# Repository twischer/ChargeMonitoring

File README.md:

ChargeMonitoring
================

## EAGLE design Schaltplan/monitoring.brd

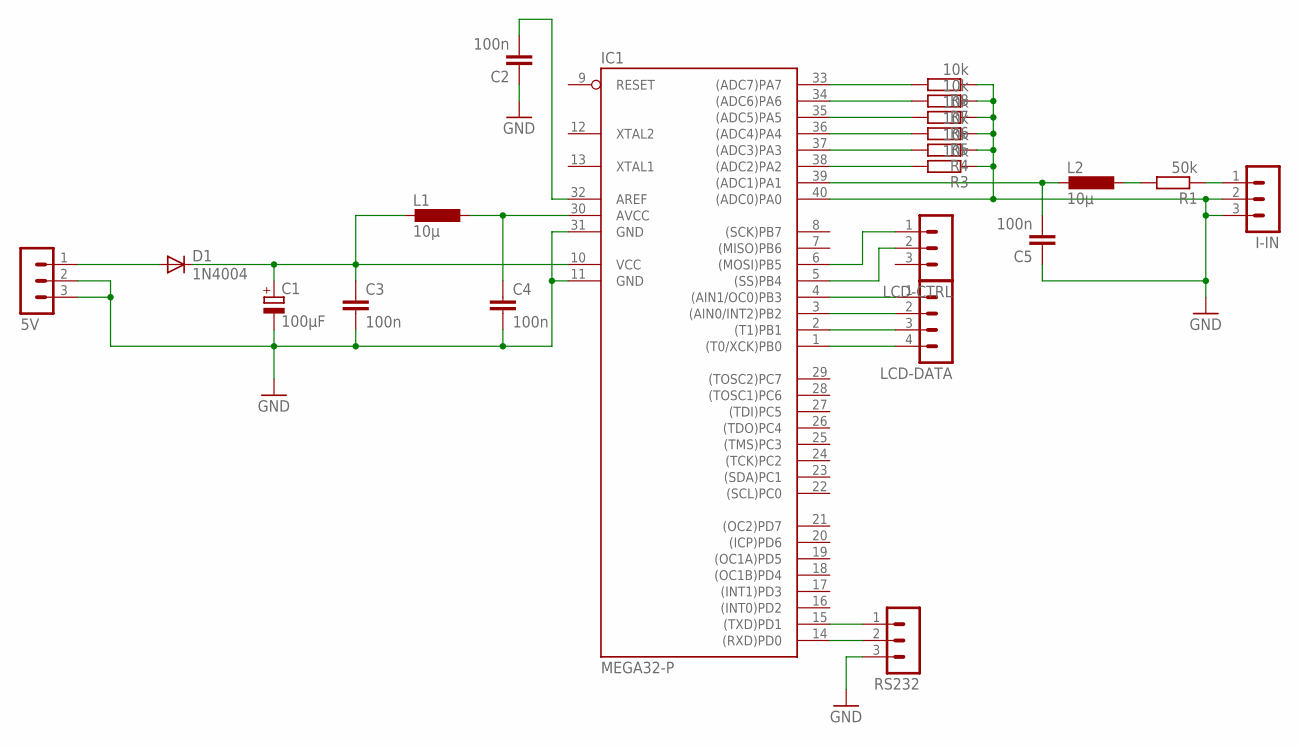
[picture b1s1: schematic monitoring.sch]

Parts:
5V: MA03-1
C1: 100µF; E5-10,5
C2, C3, C4, C5: 100n; C050-035X075
D1: 1N4004; DO41-10
I-IN: MA03-1
IC1: MEGA32-P; DIL40
L1: 10µ; 0204V
L2: 10µ; 0207/10
LCD-CTRL: MA03-1
LCD-DATA: MA04-1
R1: 50k; 0204V
R3, R4, R5, R6, R7, R8: 10k; 0204V
RS232: MA03-1

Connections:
GND: 5V.2, 5V.3, C1.-, C2.1, C3.2, C4.2, C5.1, I-IN.2, I-IN.3, IC1.11 (GND), IC1.31 (GND), IC1.40 ((ADC0)PA0), R3.1, R4.1, R5.1, R6.1, R7.1, R8.1, RS232.3
unnamed: IC1.4 ((AIN1/OC0)PB3), LCD-DATA.1
unnamed: C1.+, C3.1, D1.C, IC1.10 (VCC), L1.2
unnamed: IC1.38 ((ADC2)PA2), R3.2
unnamed: IC1.3 ((AIN0/INT2)PB2), LCD-DATA.2
unnamed: C5.2, IC1.39 ((ADC1)PA1), L2.2
unnamed: IC1.37 ((ADC3)PA3), R4.2
unnamed: IC1.2 ((T1)PB1), LCD-DATA.3
unnamed: IC1.1 ((T0/XCK)PB0), LCD-DATA.4
unnamed: IC1.5 ((SS)PB4), LCD-CTRL.2
unnamed: IC1.6 ((MOSI)PB5), LCD-CTRL.1
unnamed: 5V.1, D1.A
unnamed: IC1.36 ((ADC4)PA4), R5.2
unnamed: C2.2, IC1.32 (AREF)
unnamed: IC1.14 ((RXD)PD0), RS232.2
unnamed: IC1.15 ((TXD)PD1), RS232.1
unnamed: IC1.35 ((ADC5)PA5), R6.2
unnamed: IC1.34 ((ADC6)PA6), R7.2
unnamed: IC1.33 ((ADC7)PA7), R8.2
unnamed: C4.1, IC1.30 (AVCC), L1.1
unnamed: L2.1, R1.2
unnamed: I-IN.1, R1.1

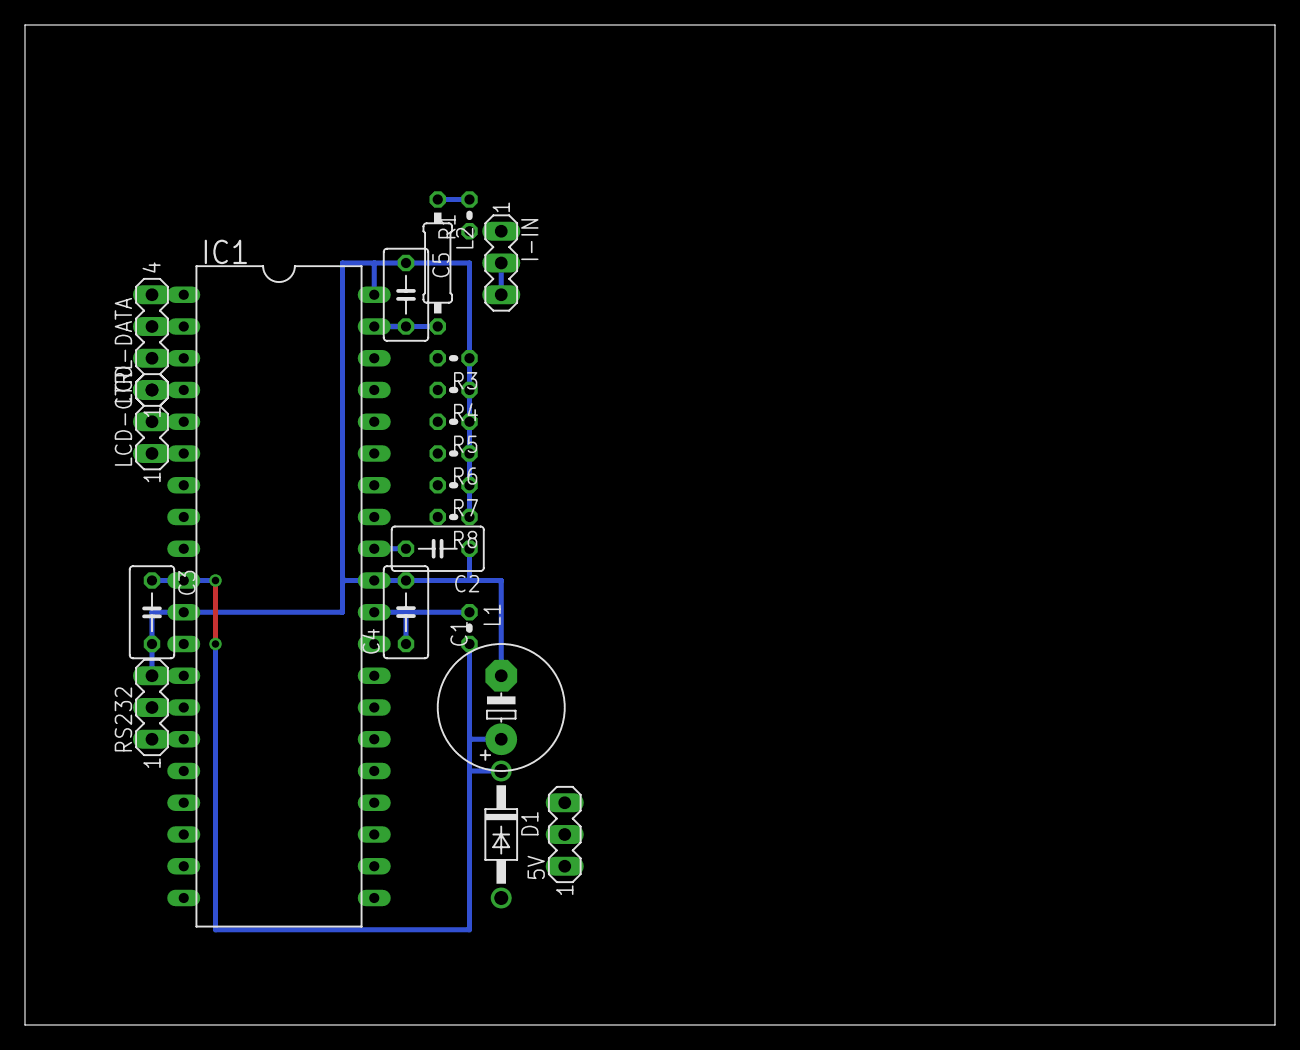
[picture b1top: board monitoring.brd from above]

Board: 2 copper layers, 100.0 x 80.0 mm, 21 parts (0 on the bottom side), 22 nets.

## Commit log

2013-08-12 Inital not working
2013-08-12 Use printf formating
2013-08-12 Add formated output
2013-09-17 Use ltoa for value to string converting
2013-09-17 Add schematic overview for hole concept
2013-09-17 Show voltages and switch between voltage and current measurments
2014-04-30 Add some induktivits to filter the adc inputs
2014-04-30 run adc conversion in main loop
2014-05-01 Add average filter for current measurment and load last capacity value from eeprom after restart
2014-06-11 Save capacity values in the eeprom for reloading on reset
2014-06-22 Use a median filter and an irr filter for the adc value which measures the current
2014-06-22 Add the adc to current and voltage convertion
